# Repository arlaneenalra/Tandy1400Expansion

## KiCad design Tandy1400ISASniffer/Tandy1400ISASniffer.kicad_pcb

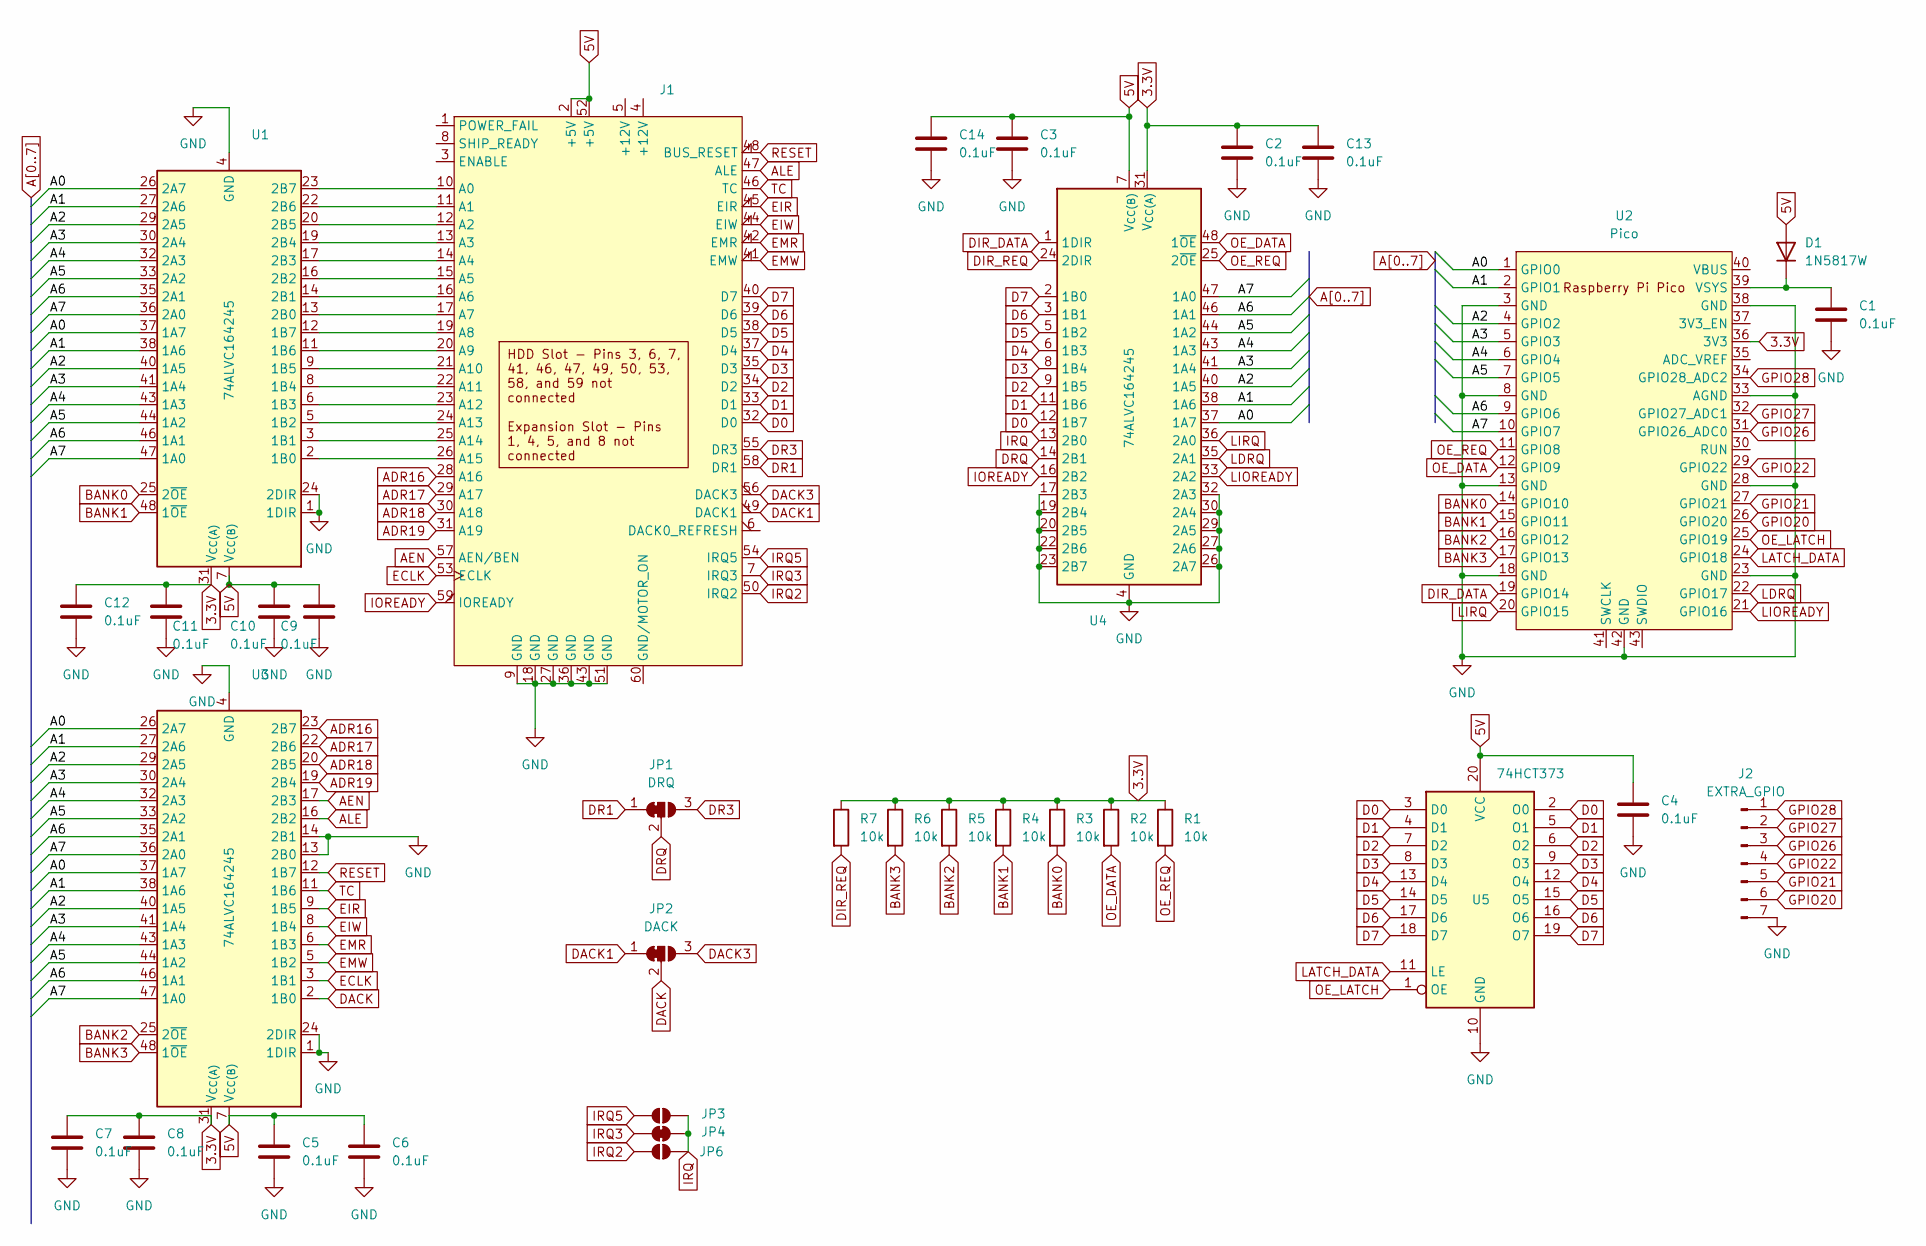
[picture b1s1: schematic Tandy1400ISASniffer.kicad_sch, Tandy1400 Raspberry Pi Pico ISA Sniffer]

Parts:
C1, C2, C3, C4, C5, C6, C7, C8, C9, C10, C11, C12, C13, C14: 0.1uF; C_0603_1608Metric; LCSC C6119861
D1: 1N5817W; D_SOD-123; LCSC C5185908
J1: TANDY_1400_EXPANSION_1
J2: EXTRA_GPIO; PinHeader_1x07_P2.54mm_Vertical
JP1: DRQ; SolderJumper-3_P1.3mm_Bridged2Bar12_RoundedPad1.0x1.5mm_Num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
JP2: DACK; SolderJumper-3_P1.3mm_Bridged2Bar12_RoundedPad1.0x1.5mm_Num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
JP3: IRQ5; SolderJumper-2_P1.3mm_Open_RoundedPad1.0x1.5mm
JP4: IRQ3; SolderJumper-2_P1.3mm_Bridged_RoundedPad1.0x1.5mm
JP6: IRQ2; SolderJumper-2_P1.3mm_Open_RoundedPad1.0x1.5mm
R1, R2, R3, R4, R5, R6, R7: 10k; R_0402_1005Metric; LCSC C25744
U1, U3, U4: 74ALVC164245; TSSOP-48_6.1x12.5mm_P0.5mm; LCSC C2652966
U2: Pico; RPi_Pico_SMD_TH
U5: 74HCT373; TSSOP-20_4.4x6.5mm_P0.65mm; LCSC C240801

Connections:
3.3V: C2.1, C7.1, C8.1, C11.1, C12.1, C13.1, R1.1, R2.1, R3.1, R4.1, R5.1, R6.1, R7.1, U1.31 (V_{CC(A)}), U1.42 (V_{CC(A)}), U2.36 (3V3), U3.31 (V_{CC(A)}), U3.42 (V_{CC(A)}), U4.31 (V_{CC(A)}), U4.42 (V_{CC(A)})
5V: C3.1, C4.1, C5.1, C6.1, C9.1, C10.1, C14.1, D1.2 (A), J1.2 (+5V), J1.52 (+5V), U1.7 (V_{CC(B)}), U1.18 (V_{CC(B)}), U3.7 (V_{CC(B)}), U3.18 (V_{CC(B)}), U4.7 (V_{CC(B)}), U4.18 (V_{CC(B)}), U5.20 (VCC)
A0: U1.26 (2A7), U1.37 (1A7), U2.1 (GPIO0), U3.26 (2A7), U3.37 (1A7), U4.37 (1A7)
A1: U1.27 (2A6), U1.38 (1A6), U2.2 (GPIO1), U3.27 (2A6), U3.38 (1A6), U4.38 (1A6)
A2: U1.29 (2A5), U1.40 (1A5), U2.4 (GPIO2), U3.29 (2A5), U3.40 (1A5), U4.40 (1A5)
A3: U1.30 (2A4), U1.41 (1A4), U2.5 (GPIO3), U3.30 (2A4), U3.41 (1A4), U4.41 (1A4)
A4: U1.32 (2A3), U1.43 (1A3), U2.6 (GPIO4), U3.32 (2A3), U3.43 (1A3), U4.43 (1A3)
A5: U1.33 (2A2), U1.44 (1A2), U2.7 (GPIO5), U3.33 (2A2), U3.44 (1A2), U4.44 (1A2)
A6: U1.35 (2A1), U1.46 (1A1), U2.9 (GPIO6), U3.35 (2A1), U3.46 (1A1), U4.46 (1A1)
A7: U1.36 (2A0), U1.47 (1A0), U2.10 (GPIO7), U3.36 (2A0), U3.47 (1A0), U4.47 (1A0)
ADR16: J1.28 (A16), U3.23 (2B7)
ADR17: J1.29 (A17), U3.22 (2B6)
ADR18: J1.30 (A18), U3.20 (2B5)
ADR19: J1.31 (A19), U3.19 (2B4)
AEN: J1.57 (AEN/BEN), U3.17 (2B3)
ALE: J1.47 (ALE), U3.16 (2B2)
BANK0: R3.2, U1.25 (2~OE), U2.14 (GPIO10)
BANK1: R4.2, U1.48 (1~OE), U2.15 (GPIO11)
BANK2: R5.2, U2.16 (GPIO12), U3.25 (2~OE)
BANK3: R6.2, U2.17 (GPIO13), U3.48 (1~OE)
D0: J1.32 (D0), U4.12 (1B7), U5.2 (O0), U5.3 (D0)
D1: J1.33 (D1), U4.11 (1B6), U5.4 (D1), U5.5 (O1)
D2: J1.34 (D2), U4.9 (1B5), U5.6 (O2), U5.7 (D2)
D3: J1.35 (D3), U4.8 (1B4), U5.8 (D3), U5.9 (O3)
D4: J1.37 (D4), U4.6 (1B3), U5.12 (O4), U5.13 (D4)
D5: J1.38 (D5), U4.5 (1B2), U5.14 (D5), U5.15 (O5)
D6: J1.39 (D6), U4.3 (1B1), U5.16 (O6), U5.17 (D6)
D7: J1.40 (D7), U4.2 (1B0), U5.18 (D7), U5.19 (O7)
DACK: JP2.2 (C), U3.2 (1B0)
DACK1: J1.49 (DACK1), JP2.1 (A)
DACK3: J1.56 (DACK3), JP2.3 (B)
DIR_DATA: U2.19 (GPIO14), U4.1 (1DIR)
DIR_REQ: R7.2, U4.24 (2DIR)
DR1: J1.58 (DR1), JP1.1 (A)
DR3: J1.55 (DR3), JP1.3 (B)
DRQ: JP1.2 (C), U4.14 (2B1)
ECLK: J1.53 (ECLK), U3.3 (1B1)
EIR: J1.45 (EIR), U3.9 (1B5)
EIW: J1.44 (EIW), U3.8 (1B4)
EMR: J1.42 (EMR), U3.6 (1B3)
EMW: J1.41 (EMW), U3.5 (1B2)
GND: C1.2, C2.2, C3.2, C4.2, C5.2, C6.2, C7.2, C8.2, C9.2, C10.2, C11.2, C12.2, C13.2, C14.2, J1.9 (GND), J1.18 (GND), J1.27 (GND), J1.36 (GND), J1.43 (GND), J1.51 (GND), J2.7, U1.1 (1DIR), U1.4 (GND), U1.10 (GND), U1.15 (GND), U1.21 (GND), U1.24 (2DIR), U1.28 (GND), U1.34 (GND), U1.39 (GND), U1.45 (GND), U2.3 (GND), U2.8 (GND), U2.13 (GND), U2.18 (GND), U2.23 (GND), U2.28 (GND), U2.33 (AGND), U2.38 (GND), U2.42 (GND), U3.1 (1DIR), U3.4 (GND), U3.10 (GND), U3.13 (2B0), U3.14 (2B1), U3.15 (GND), U3.21 (GND), U3.24 (2DIR), U3.28 (GND), U3.34 (GND), U3.39 (GND), U3.45 (GND), U4.4 (GND), U4.10 (GND), U4.15 (GND), U4.17 (2B3), U4.19 (2B4), U4.20 (2B5), U4.21 (GND), U4.22 (2B6), U4.23 (2B7), U4.26 (2A7), U4.27 (2A6), U4.28 (GND), U4.29 (2A5), U4.30 (2A4), U4.32 (2A3), U4.34 (GND), U4.39 (GND), U4.45 (GND), U5.10 (GND)
GPIO20: J2.6, U2.26 (GPIO20)
GPIO21: J2.5, U2.27 (GPIO21)
GPIO22: J2.4, U2.29 (GPIO22)
GPIO26: J2.3, U2.31 (GPIO26_ADC0)
GPIO27: J2.2, U2.32 (GPIO27_ADC1)
GPIO28: J2.1, U2.34 (GPIO28_ADC2)
IOREADY: J1.59 (IOREADY), U4.16 (2B2)
IRQ: JP3.2 (B), JP4.2 (B), JP6.2 (B), U4.13 (2B0)
IRQ2: J1.50 (IRQ2), JP6.1 (A)
IRQ3: J1.7 (IRQ3), JP4.1 (A)
IRQ5: J1.54 (IRQ5), JP3.1 (A)
LATCH_DATA: U2.24 (GPIO18), U5.11 (LE)
LDRQ: U2.22 (GPIO17), U4.35 (2A1)
LIOREADY: U2.21 (GPIO16), U4.33 (2A2)
LIRQ: U2.20 (GPIO15), U4.36 (2A0)
unnamed: C1.1, D1.1 (K), U2.39 (VSYS)
unnamed: J1.10 (A0), U1.23 (2B7)
unnamed: J1.11 (A1), U1.22 (2B6)
unnamed: J1.12 (A2), U1.20 (2B5)
unnamed: J1.13 (A3), U1.19 (2B4)
unnamed: J1.14 (A4), U1.17 (2B3)
unnamed: J1.15 (A5), U1.16 (2B2)
unnamed: J1.16 (A6), U1.14 (2B1)
unnamed: J1.17 (A7), U1.13 (2B0)
unnamed: J1.19 (A8), U1.12 (1B7)
unnamed: J1.20 (A9), U1.11 (1B6)
unnamed: J1.21 (A10), U1.9 (1B5)
unnamed: J1.22 (A11), U1.8 (1B4)
unnamed: J1.23 (A12), U1.6 (1B3)
unnamed: J1.24 (A13), U1.5 (1B2)
unnamed: J1.25 (A14), U1.3 (1B1)
unnamed: J1.26 (A15), U1.2 (1B0)
OE_DATA: R2.2, U2.12 (GPIO9), U4.48 (1~OE)
OE_LATCH: U2.25 (GPIO19), U5.1 (OE)
OE_REQ: R1.2, U2.11 (GPIO8), U4.25 (2~OE)
RESET: J1.48 (BUS_RESET), U3.12 (1B7)
TC: J1.46 (TC), U3.11 (1B6)

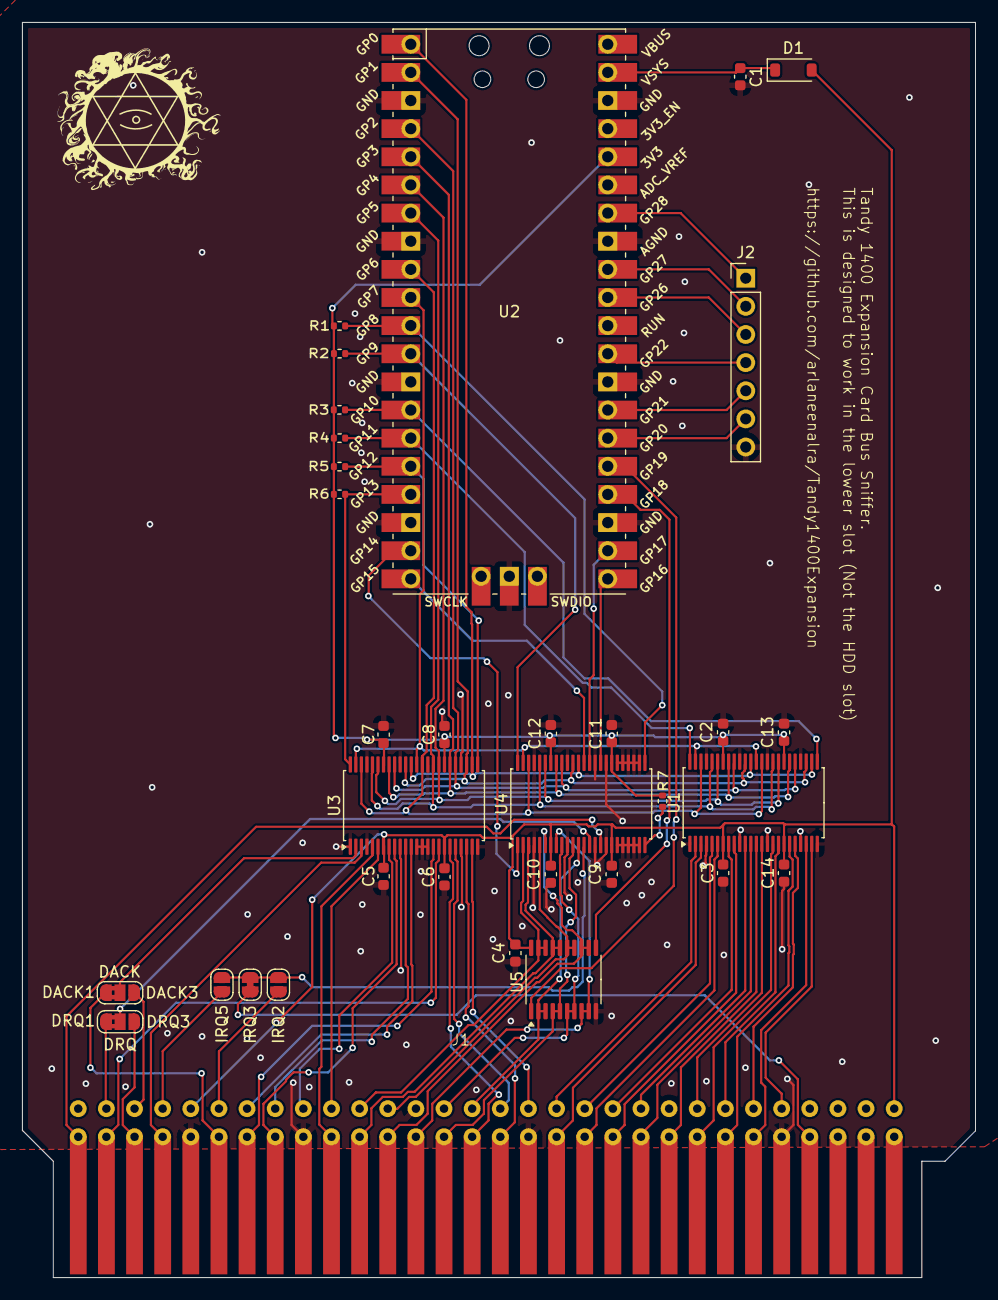
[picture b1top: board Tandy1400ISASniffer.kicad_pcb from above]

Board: 2 copper layers, 86.0 x 113.3 mm, 34 parts (0 on the bottom side), 79 nets.

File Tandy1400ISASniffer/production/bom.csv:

Designator,Footprint,Quantity,Value,LCSC Part #
"C1, C10, C11, C12, C13, C14, C2, C3, C4, C5, C6, C7, C8, C9",0603,14,0.1uF,C6119861
D1,D_SOD-123,1,1N5817W,C5185908
J2,PinHeader_1x07_P2.54mm_Vertical,1,EXTRA_GPIO,
"R1, R2, R3, R4, R5, R6, R7",0402,7,10k, C25744
"U1, U3, U4",TSSOP-48_6.1x12.5mm_P0.5mm,3,74ALVC164245,C2652966
U2,RPi_Pico_SMD_TH,1,Pico,
U5,TSSOP-20_4.4x6.5mm_P0.65mm,1,74HCT373,C240801

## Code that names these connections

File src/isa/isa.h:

#pragma once

#include "pico/stdlib.h"
#include "hardware/gpio.h"
#include "hardware/pio.h"

#include <inttypes.h>

#define SET_BIT(b) (1u << b)

/**
 * Data GPIOs
 */
#define DATA_0 0
#define DATA_1 1
#define DATA_2 2
#define DATA_3 3
#define DATA_4 4
#define DATA_5 5
#define DATA_6 6
#define DATA_7 7

/**
 * Define bus control pins.
 */
#define OE_REQ 8

#define LIRQ 15
#define LDRQ 17
#define LIOREADY 16

#define OE_DATA 9
#define DIR_DATA 14
#define LATCH_DATA 18
#define OE_LATCH 19

#define BANK_0 10
#define BANK_1 11
#define BANK_2 12
#define BANK_3 13

#define GPIO20 20
#define GPIO21 21
#define GPIO22 22
#define GPIO26 26
#define GPIO27 27
#define GPIO28 28


/**
 * Special data pins
 */
#define AEN          DATA_4
#define ALE          DATA_5
#define RESET        DATA_0
#define TC           DATA_1
#define IO_READ      DATA_2
#define IO_WRITE     DATA_3
#define MEM_READ     DATA_4
#define MEM_WRITE    DATA_5
#define E_CLK        DATA_6
#define DACK         DATA_7

/**
 * IO Masks
 */

// Data operations only happen on pins 0-8
#define DATA_MASK          0x000000FFu
#define CONTROL_MASK       0x000FFF00u

// We control the first 20 GPIO pins
#define DATA_FUNCTION_MASK 0x000FFFFFu

#define OE_MASK (       \
    SET_BIT(OE_DATA)    \
    | SET_BIT(OE_REQ)   \
    | SET_BIT(BANK_0)   \
    | SET_BIT(BANK_1)   \
    | SET_BIT(BANK_2)   \
    | SET_BIT(BANK_3)   \
    )

// Bank pins
#define BUS_BANK_0 SET_BIT(BANK_0)
#define BUS_BANK_1 SET_BIT(BANK_1)
#define BUS_BANK_2 SET_BIT(BANK_2)
#define BUS_BANK_3 SET_BIT(BANK_3)

// Specific IO masks
#define BUS_AEN SET_BIT(AEN)
#define BUS_ALE SET_BIT(ALE)

#define BUS_RESET SET_BIT(RESET)
#define BUS_TC SET_BIT(TC)
#define BUS_E_IO_READ SET_BIT(IO_READ)
#define BUS_E_IO_WRITE SET_BIT(IO_WRITE)
#define BUS_E_MEM_READ SET_BIT(MEM_READ)
#define BUS_E_MEM_WRITE SET_BIT(MEM_WRITE)
#define BUS_E_CLK SET_BIT(E_CLK)
#define BUS_DACK SET_BIT(DACK)

#define BUS_OP_COMMAND (               \
    BUS_E_IO_READ | BUS_E_IO_WRITE |   \
    BUS_E_MEM_READ | BUS_E_MEM_WRITE   \
)

#define BUS_OP_READ (BUS_E_MEM_READ | BUS_E_IO_READ)
#define BUS_OP_WRITE (BUS_E_MEM_WRITE | BUS_E_IO_WRITE)

#define BUS_OP_MEM (BUS_E_MEM_WRITE | BUS_E_MEM_READ)
#define BUS_OP_IO (BUS_E_IO_WRITE | BUS_E_IO_READ)

/**
 * Structure representing the current state of the attached ISA
 * bus. 
 *
 */
typedef struct isa_bus_state_type {
  uint32_t addr; // The bus actually uses 20bit addresses,
                          // but there are no 20bit types.
  
  uint8_t operation;
  uint8_t data;
} isa_bus_state_t;


/**
 * Initializes all of the GPIO pins etc for reading the isa bus.
 */
void init_isa_bus();

void isa_read_operation(isa_bus_state_t *bus);
void isa_wait_for_addr(isa_bus_state_t *bus);

void __isa_set_bank(uint32_t bank);
#define isa_set_bank(b) __isa_set_bank(SET_BIT(b))

void isa_read_bus(isa_bus_state_t *bus);

// Include the isa_mem pio header
#include "isa_mem.pio.h"

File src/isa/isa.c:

#include <strings.h>

#include "isa.h"

#define ISA_PIO pio0
#define ISA_ADDR_SM 0

/**
 * ISA reference timings https://gist.github.com/PhirePhly/2209518
 */

void init_isa_bus() {
  // Disable pulls
  uint32_t gpio_mask = DATA_FUNCTION_MASK;
  for (int i = 0; i < 32; i ++ ) {
    // We're assuming a continuous block of gpios 
    if (!(gpio_mask & 1u )) {
      break;
    }
      
     gpio_set_pulls(i, false, false);
     //gpio_set_input_hysteresis_enabled(i, false);
     gpio_set_slew_rate(i, GPIO_SLEW_RATE_FAST); 

     gpio_mask >>= 1;
  }

  // Set everything to inputs for now.
  gpio_set_dir_in_masked(DATA_FUNCTION_MASK);
  gpio_put_masked(CONTROL_MASK, OE_MASK | SET_BIT(OE_LATCH));
  gpio_set_function_masked(CONTROL_MASK, GPIO_FUNC_SIO);

  // Control lines are always outputs
  gpio_set_dir_out_masked(CONTROL_MASK);

  gpio_put(DIR_DATA, false);

  // Setup the isa address reader pio.
  uint isa_addr_offset = pio_add_program(ISA_PIO, &isa_addr_program);
  pio_sm_claim(ISA_PIO, ISA_ADDR_SM);
  isa_addr_pio_init(ISA_PIO, ISA_ADDR_SM, isa_addr_offset);
}

/**
 * Bank output enables are all active low.
 * 
 */
void __not_in_flash_func(__isa_set_bank)(uint32_t bank) {
  gpio_put_masked(OE_MASK, ~bank);

  pico_default_asm_volatile("nop");
  pico_default_asm_volatile("nop");
  pico_default_asm_volatile("nop");
  pico_default_asm_volatile("nop");
}

/**
 * Reads an address from the bus.
 */
void __not_in_flash_func(isa_read_operation)(isa_bus_state_t *bus) {
  uint32_t buf, buf1, buf2;

  // Pull the 20bit address
  isa_set_bank(BANK_0);
  buf = gpio_get_all();

  isa_set_bank(BANK_1);
  buf1 = gpio_get_all();

  isa_set_bank(BANK_2);
  buf2 = gpio_get_all();

  bus->addr = (buf & DATA_MASK) |
    ((buf1 & DATA_MASK) << 8) |
    ((buf1 & 0x0F) << 16);
//  bus->addr = buf & DATA_MASK;

  // If we're in a write operation, data should be valid at this point.
  gpio_put(DIR_DATA, false);
  isa_set_bank(OE_DATA);
  bus->data = gpio_get_all() & DATA_MASK;
}


/**
 * Waits for ALE to go high then low.
 * Addresses are considered valid when ALE goes low.
 */
void __not_in_flash_func(isa_wait_for_addr)(isa_bus_state_t *bus) {
  uint32_t bank2, bank1, bank0;

  isa_set_bank(BANK_2);
  // Wait for rising edge
  do {
    tight_loop_contents();
    bank2 = gpio_get_all();
  } while ((bank2 & BUS_ALE) != BUS_ALE);

  // Wait for falling edge
  do {
    tight_loop_contents();
    bank2 = gpio_get_all();
  } while ((bank2 & BUS_ALE) != 0);

  // Pull the 20bit address
  isa_set_bank(BANK_0);
  bank0 = gpio_get_all();

  isa_set_bank(BANK_1);
  bank1 = gpio_get_all();

  bus->addr = (bank0 & DATA_MASK) |
    ((bank1 & DATA_MASK) << 8) |
    ((bank2 & 0x0F) << 16);

  isa_set_bank(BANK_3);
  bus->operation = gpio_get_all() & DATA_MASK;

  gpio_put(DIR_DATA, false);
  isa_set_bank(OE_DATA);
  bus->data = gpio_get_all() & DATA_MASK;
}

/**
 * Use PIO to read an address and data byte
 */
void __not_in_flash_func(isa_read_bus)(isa_bus_state_t * bus) {
  uint32_t raw_bus = pio_sm_get_blocking(ISA_PIO, ISA_ADDR_SM);

  bus->addr = (raw_bus &  0x0FFFFF00) >> 8; // mask off address
  bus->operation = (raw_bus & 0x000000FF); // Mask of operation
  bus->data = 0x00; // not reading data right now. 
}

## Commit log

2024-12-31 Add initial board design.
2024-12-31 Add build.
2024-12-31 Add build requirements.
2024-12-31 Fix typo.
2024-12-31 Fix step names.
2024-12-31 Use https submodule urls
2024-12-31 Fix working directory.
2025-01-19 Starting work on the software.
2025-01-20 Caught the boot addresses, so this PIO stuff seems to be working.
